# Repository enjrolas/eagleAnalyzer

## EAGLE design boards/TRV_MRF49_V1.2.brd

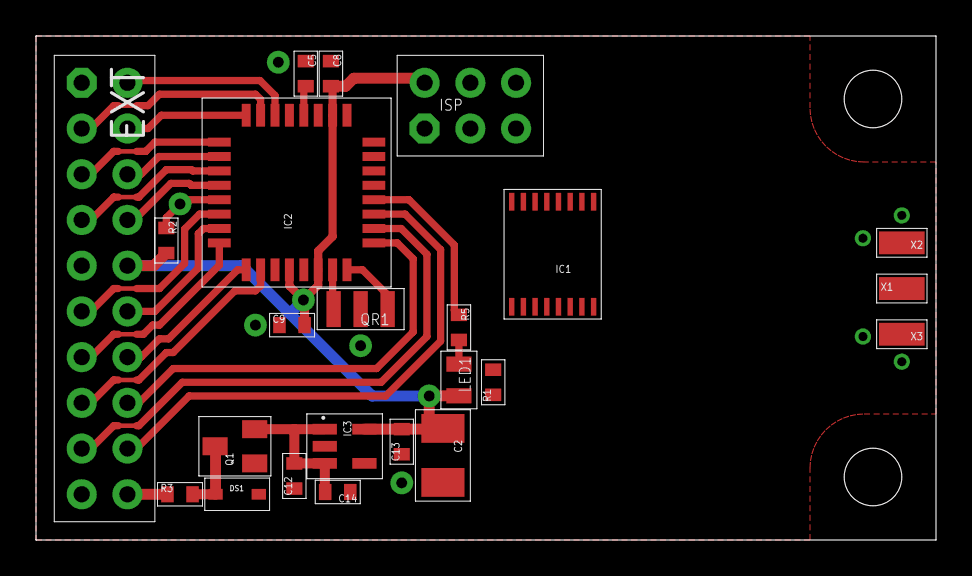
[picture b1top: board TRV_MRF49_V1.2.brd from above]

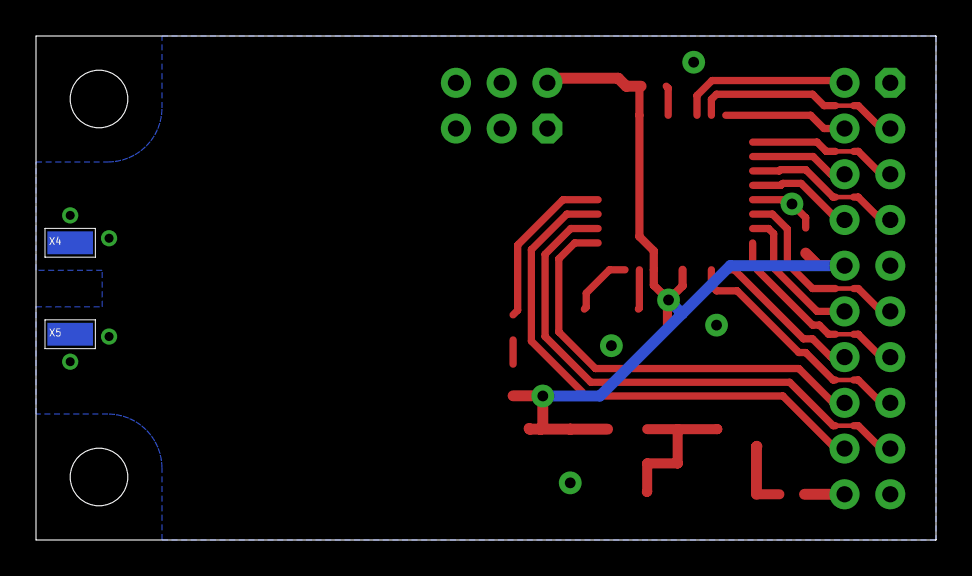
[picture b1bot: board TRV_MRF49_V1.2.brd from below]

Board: 2 copper layers, 50.0 x 28.0 mm, 25 parts (2 on the bottom side), 31 nets.

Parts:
C2: 10u; SMC_B
C5, C8, C9, C14: 100n; 0603
C12, C13: 1u; 0603
DS1: PESD12VL1BA; SOD323
EXT: EXT; ML20S
IC1: TSSOP16
IC2: MEGA328P-AU; TQFP32-08
IC3: LP2992-IM5-3.3; SOT23-5
ISP: ISP; ML6S
LED1: LEDR; 0805
Q1: IRLML9301; SOT23
QR1: 8M; CR
R1, R2: 10k; 0603
R3: 0R; 0603
R5: 330R; 0603
X1: ANT; S2.54/1.27
X2, X3, X4, X5: GND; S2.54/1.27

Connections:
+3V3: C2.+, C8.2, C9.2, C13.2, EXT.10, IC2.4, IC2.6, IC2.18, IC3.5, ISP.2, LED1.C, R1.1, R2.2
GND: C2.-, C5.1, C8.1, C9.1, C12.1, C13.1, C14.1, DS1.A, EXT.9, EXT.19, IC1.11, IC2.3, IC2.5, IC2.21, IC3.2, ISP.6, Q1.1, QR1.M, X2.1, X3.1, X4.1, X5.1
MISO: IC1.4, IC2.16, ISP.1
MOSI: IC1.1, IC2.15, ISP.4
unnamed: EXT.2, IC2.22
unnamed: DS1.C, Q1.3, R3.2
unnamed: C5.2, IC2.20
unnamed: IC2.8, QR1.1
unnamed: IC2.7, QR1.2
unnamed: EXT.20, R3.1
unnamed: IC2.12, R5.1
unnamed: C12.2, C14.2, IC3.1, IC3.3, Q1.2
unnamed: LED1.A, R5.2
PC0: EXT.3, IC2.23
PC1: EXT.4, IC2.24
PC2: EXT.5, IC2.25
PC3: EXT.6, IC2.26
PC4: EXT.7, IC2.27
PC5: EXT.8, IC2.28
PD2: EXT.13, IC2.32
PD3: EXT.14, IC2.1
PD4: EXT.15, IC2.2
PD5: EXT.16, IC2.9
PD6: EXT.17, IC2.10
PD7: EXT.18, IC2.11
RIRQ: IC1.5, IC2.13
RSEL: IC1.3, IC2.14, R1.2
RST: IC2.29, ISP.5, R2.1
RXD: EXT.11, IC2.30
SCK: IC1.2, IC2.17, ISP.3
TXD: EXT.12, IC2.31

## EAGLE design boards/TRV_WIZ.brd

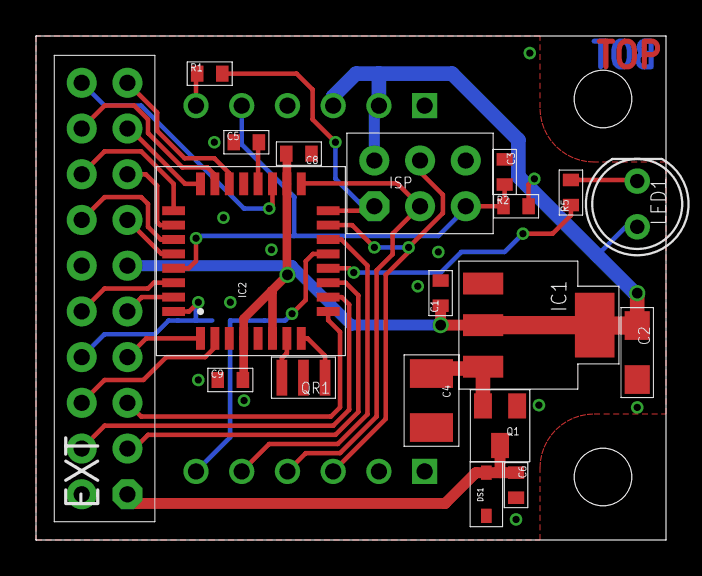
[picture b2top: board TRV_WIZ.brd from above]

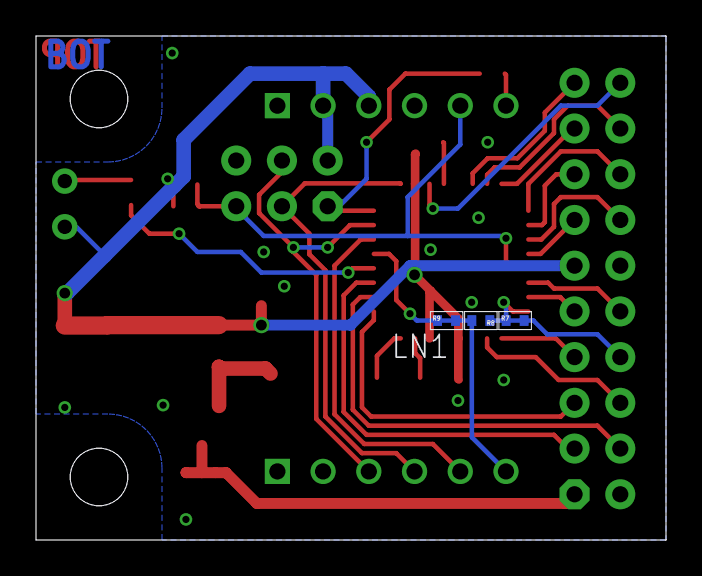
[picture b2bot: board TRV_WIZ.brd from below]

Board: 2 copper layers, 35.0 x 28.0 mm, 23 parts (4 on the bottom side), 32 nets.

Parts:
C1: 1u; 0603
C2: 10u 6V; SMC_A
C3, C5, C6, C8, C9: 100n; 0603
C4: 10u 20V; SMC_B
DS1: PESD12VL1BA; SOD323
EXT: EXT; ML20S
IC1: LD1117S33TR; SOT223
IC2: MEGA328P-AU; TQFP32-08
ISP: ISP; ML6S
LED1: LEDR; T1-3/4
LN1: WIZ820IO
Q1: IRLML9301TRPBF; SOT23
QR1: 8M; CSTCE
R1, R5: 330R; 0603
R2: 10k; 0603
R7, R8, R9: cfg; 0402

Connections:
+3V3: C1.1, C2.+, C8.2, C9.2, EXT.11, IC1.2, IC1.4, IC2.4, IC2.6, IC2.18, ISP.2, LED1.A, LN1.J2.2, LN1.J2.3, R2.2
GND: C1.2, C2.-, C3.1, C4.-, C5.1, C6.2, C8.1, C9.1, DS1.C, EXT.2, EXT.12, IC1.1, IC2.3, IC2.5, IC2.21, ISP.6, LN1.J1.1, LN1.J1.2, LN1.J2.1, Q1.1, QR1.G
MISO: IC2.16, ISP.1, R1.2
MOSI: IC2.15, ISP.4, LN1.J1.3
unnamed: LN1.J2.6, R1.1
unnamed: C6.1, DS1.A, EXT.1, Q1.3
unnamed: EXT.19, IC2.22
unnamed: C4.+, IC1.3, Q1.2
unnamed: C5.2, IC2.20
unnamed: IC2.8, QR1.A
unnamed: IC2.7, QR1.B
unnamed: IC2.12, R5.1
unnamed: EXT.8, IC2.32, R7.1, R7.2, R8.1
unnamed: EXT.20, IC2.19
unnamed: LED1.C, R5.2
PC0: EXT.18, IC2.23
PC1: EXT.17, IC2.24
PC2: EXT.16, IC2.25
PC3: EXT.15, IC2.26
PC4: EXT.14, IC2.27
PC5: EXT.13, IC2.28
PD3: EXT.7, IC2.1
PD4: EXT.6, IC2.2
PD5: EXT.5, IC2.9
PD6: EXT.4, IC2.10
PD7: EXT.3, IC2.11
RST: C3.2, IC2.29, ISP.5, LN1.J2.5, R2.1
RXD: EXT.10, IC2.30
SCK: IC2.17, ISP.3, LN1.J1.4
TXD: EXT.9, IC2.31
WIRQ: IC2.13, LN1.J1.6, R8.2, R9.1, R9.2
WSEL: IC2.14, LN1.J1.5

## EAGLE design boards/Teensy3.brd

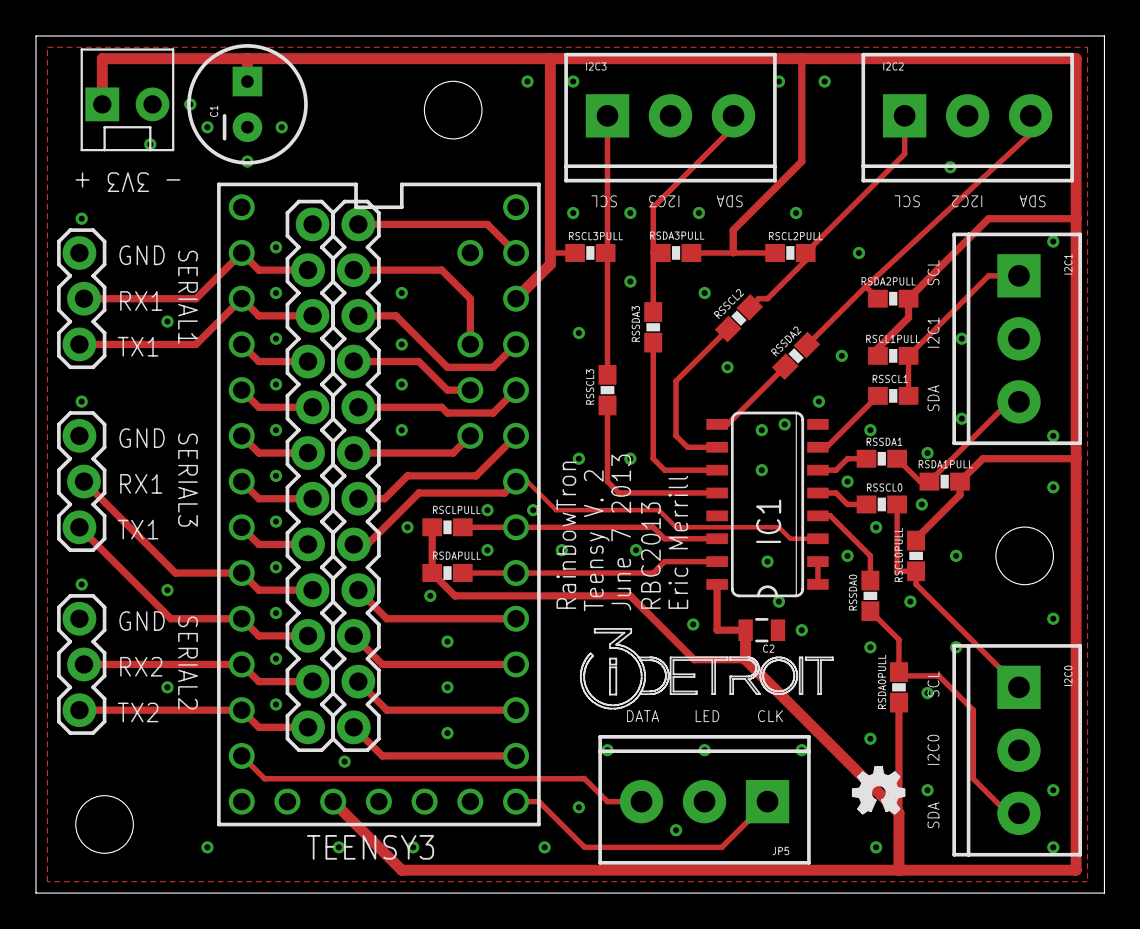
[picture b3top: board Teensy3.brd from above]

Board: 2 copper layers, 59.4 x 47.6 mm, 35 parts (0 on the bottom side), 45 nets.

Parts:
C1: CPOL-RADIAL-100UF-25V
C2: .1uF; 0805
I2C0, I2C1, I2C2, I2C3: SCREWTERMINAL-3.5MM-3
IC1: SO16
JP1, JP2: 1X12_LOCK
JP5: SCREWTERMINAL-3.5MM-3
PWR: MOLEX-1X2_LOCK
RSCL0PULL, RSCL1PULL, RSCL2PULL, RSCL3PULL: 3.3k; 0603-RES
RSCLPULL: 3.3k; 0603-RES
RSDA0PULL, RSDA1PULL, RSDA2PULL, RSDA3PULL: 3.3k; 0603-RES
RSDAPULL: 3.3k; 0603-RES
RSSCL0, RSSCL1, RSSCL2, RSSCL3: 200; 0603-RES
RSSDA0, RSSDA1, RSSDA2, RSSDA3: 200; 0603-RES
SERIAL1, SERIAL2, SERIAL3: 1X03_LOCK
TEENSY3: TEENSY_3.0+4
U$1: I3DETROITVEC14MM
U$2: OSHW_FILLX100_NOTEXT

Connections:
GND: C1.2, C2.1, I2C0.2, I2C1.2, I2C2.2, I2C3.2, IC1.1, IC1.2, IC1.8, IC1.13, JP1.12, JP5.2, PWR.2, SERIAL1.3, SERIAL2.3, SERIAL3.3, TEENSY3.GND, TEENSY3.GND1
unnamed: IC1.12, RSSCL3.1
unnamed: IC1.11, RSSDA3.1
unnamed: IC1.10, RSSCL2.1
unnamed: JP1.1, SERIAL2.1, TEENSY3.10
unnamed: IC1.9, RSSDA2.1
unnamed: IC1.7, RSSCL1.2
unnamed: IC1.6, RSSDA1.2
unnamed: IC1.5, RSSCL0.2
unnamed: IC1.4, RSSDA0.2
unnamed: JP1.2, SERIAL2.2, TEENSY3.9
unnamed: JP1.4, SERIAL3.2, TEENSY3.7
unnamed: JP1.3, SERIAL3.1, TEENSY3.8
unnamed: IC1.3, JP2.5, TEENSY3.20/A6
unnamed: JP5.3, TEENSY3.11
unnamed: JP1.5, TEENSY3.6
unnamed: JP1.6, TEENSY3.5
unnamed: JP1.7, TEENSY3.4
unnamed: JP1.8, TEENSY3.3
unnamed: JP1.9, TEENSY3.2
unnamed: JP2.1, TEENSY3.14/A0
unnamed: JP2.2, TEENSY3.15/A1
unnamed: JP5.1, TEENSY3.13
unnamed: JP2.3, TEENSY3.16/A2
unnamed: JP2.4, TEENSY3.17/A3
unnamed: JP2.6, TEENSY3.21/A7
unnamed: JP2.7, TEENSY3.A11
unnamed: JP2.8, TEENSY3.22/A8
unnamed: JP2.9, TEENSY3.A10
unnamed: JP2.10, TEENSY3.23/A9
unnamed: JP2.12, TEENSY3.AGND
unnamed: JP2.11, TEENSY3.AREF
RX1: JP1.11, SERIAL1.2, TEENSY3.0
SCL: IC1.14, RSCLPULL.2, TEENSY3.19/A5
SCL0: I2C0.1, RSCL0PULL.1, RSSCL0.1
SCL1: I2C1.1, RSCL1PULL.1, RSSCL1.1
SCL2: I2C2.1, RSCL2PULL.1, RSSCL2.2
SCL3: I2C3.1, RSCL3PULL.1, RSSCL3.2
SDA: IC1.15, RSDAPULL.2, TEENSY3.18/A4
SDA0: I2C0.3, RSDA0PULL.1, RSSDA0.1
SDA1: I2C1.3, RSDA1PULL.1, RSSDA1.1
SDA2: I2C2.3, RSDA2PULL.1, RSSDA2.2
SDA3: I2C3.3, RSDA3PULL.1, RSSDA3.2
TX1: JP1.10, SERIAL1.1, TEENSY3.1
VCC: C1.1, C2.2, IC1.16, PWR.1, RSCL0PULL.2, RSCL1PULL.2, RSCL2PULL.2, RSCL3PULL.2, RSCLPULL.1, RSDA0PULL.2, RSDA1PULL.2, RSDA2PULL.2, RSDA3PULL.2, RSDAPULL.1, TEENSY3.3.3V, TEENSY3.3.3V1

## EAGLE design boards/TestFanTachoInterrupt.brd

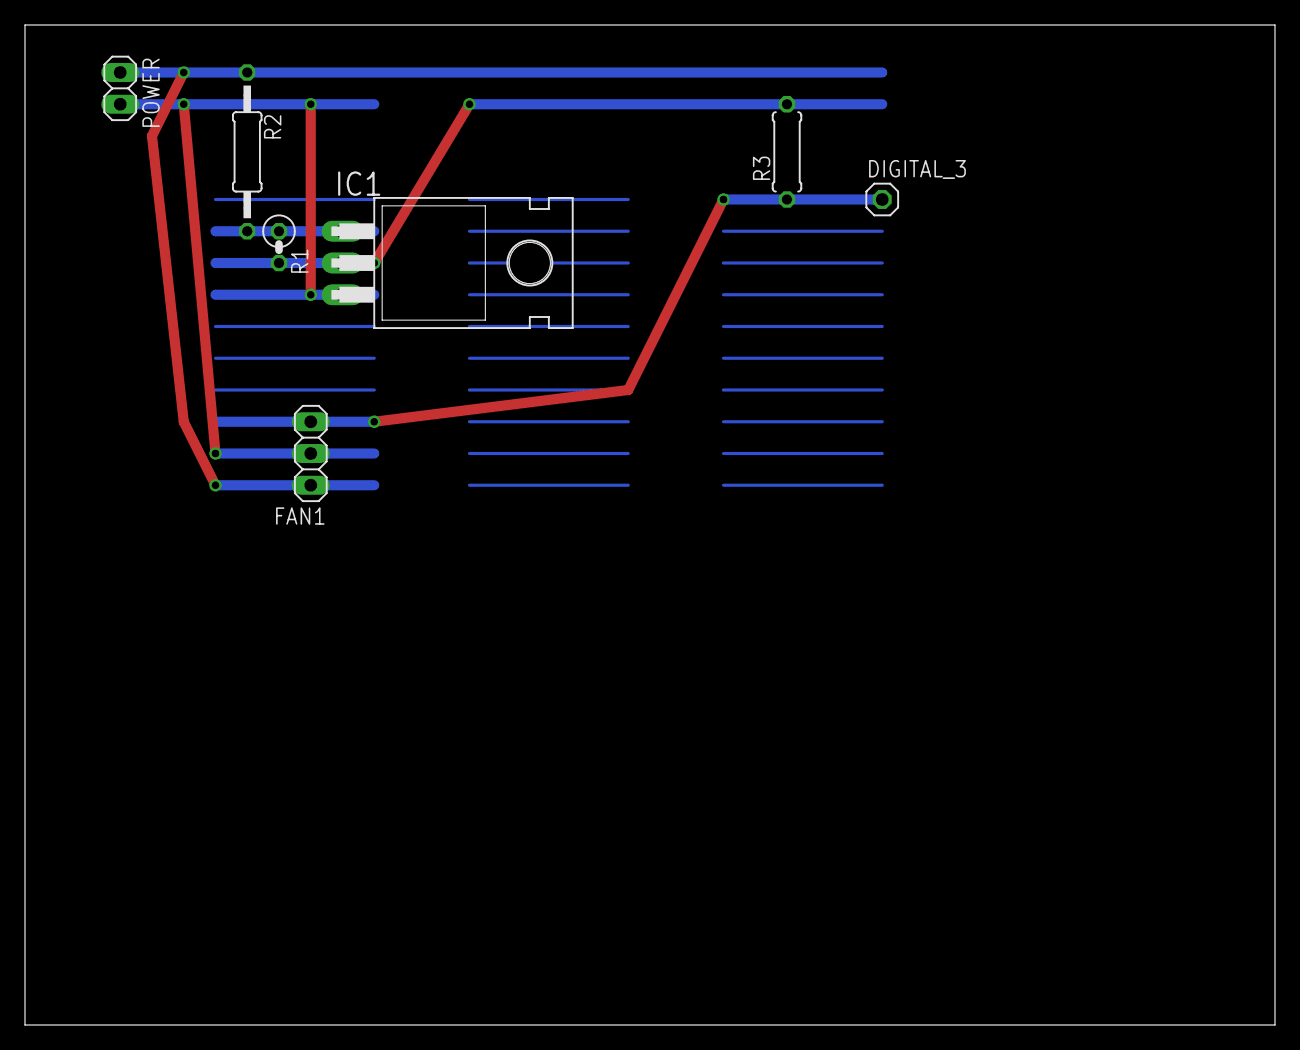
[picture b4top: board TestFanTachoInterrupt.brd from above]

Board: 2 copper layers, 100.0 x 80.0 mm, 7 parts (0 on the bottom side), 5 nets.

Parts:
DIGITAL_3: 1X01
FAN1: 1X03
IC1: 317T; TO220H
POWER: 1X02
R1: 330; 0207/2V
R2: 1k; 0207/12
R3: 10k; 0207/7

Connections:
+12V: FAN1.2, IC1.3, POWER.2
FAN1_TACHO: DIGITAL_3.1, FAN1.1, R3.1
GND: FAN1.3, POWER.1, R2.1
unnamed: IC1.1, R1.1, R2.2
VCC: IC1.2, R1.2, R3.2

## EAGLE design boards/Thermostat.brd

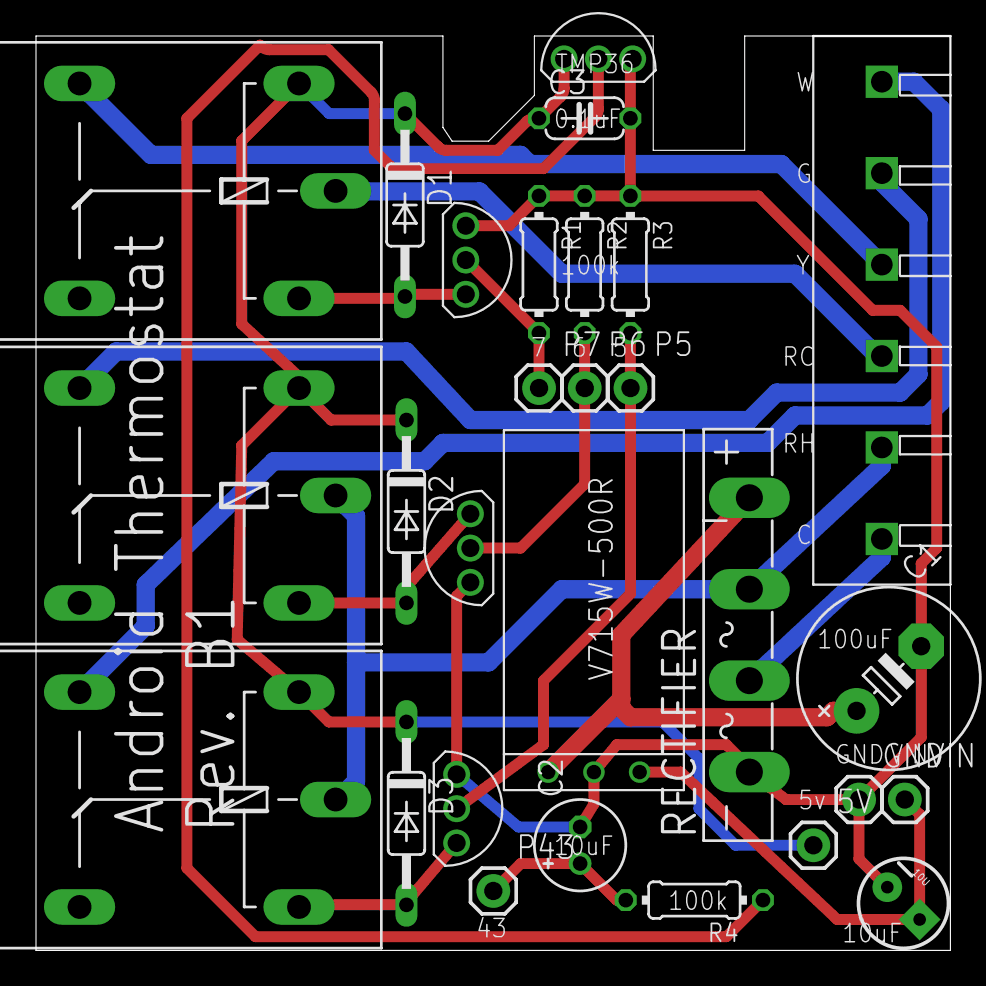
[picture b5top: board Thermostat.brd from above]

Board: 2 copper layers, 50.8 x 50.8 mm, 28 parts (0 on the bottom side), 18 nets.

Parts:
5V: 1X01
10U: CPOL-RADIAL-10UF-25V
C1: E5-10,5
C2: E2-5
C3: C050-024X044
D1, D2, D3: DO35-10
GND: 1X01
K1, K2, K3: G5LE
P5, P6, P7, P43: 1X01
R1, R2, R3, R4: 0204/7
RECTIFIER: GBU4S
U$1: TMP36
U$2: V715W-500R; SWITCHINGREGULATOR
U$3: PHOENIX-651-1935200; PHOENIX_E_5MM_6PIN
U$4, U$5, U$6: TRANSISTOR
VIN: 1X01

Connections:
+5V: 5V.1, C3.1, D1.C, D2.C, D3.C, K1.1, K2.1, K3.1, U$1.VC1
GND: 10U.2, C1.-, C2.-, C3.2, GND.1, R1.1, R2.1, R3.1, RECTIFIER.-, U$1.GND3, U$2.GND, U$4.S, U$5.S, U$6.S
unnamed: K1.P, U$3.P$3
unnamed: P6.1, R2.2, U$5.G
unnamed: D2.A, K2.2, U$5.D
unnamed: C2.+, P43.1, R4.2
unnamed: R4.1, U$1.OUT2
unnamed: P7.1, R1.2, U$6.G
unnamed: D1.A, K1.2, U$6.D
unnamed: K2.P, K3.P, RECTIFIER.AC1, U$3.P$2
unnamed: 10U.1, U$2.VO, VIN.1
unnamed: K3.S, U$3.P$6
unnamed: K1.S, U$3.P$4
unnamed: K2.S, U$3.P$5
unnamed: P5.1, R3.2, U$4.G
unnamed: D3.A, K3.2, U$4.D
unnamed: RECTIFIER.AC2, U$3.P$1
unnamed: C1.+, RECTIFIER.+, U$2.VI

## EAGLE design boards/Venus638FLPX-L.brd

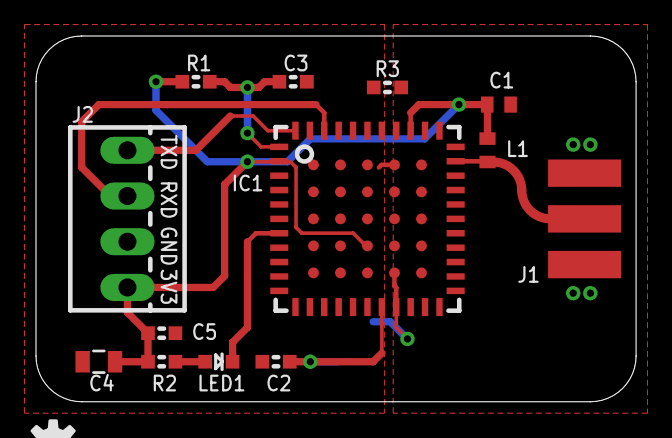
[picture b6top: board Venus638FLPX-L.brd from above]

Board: 2 copper layers, 33.3 x 20.3 mm, 15 parts (1 on the bottom side), 10 nets.

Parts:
B1: Keystone 3000; BATTCON_12MM
C1: 22pF; C0402
C2, C3, C5: 100nF; 0603
C4: 10µF; 0805
IC1: VENUS638FLPX-L; VENUS638FLPX
J1: Antenna; SMA-EDGE
J2: Interface; 22-23-2041
L1: 33nH; C0402
LED1: Status; LED-0603
R1: 33kΩ; 0603
R2: 470Ω; 0603
R3: 0Ω; 0603
SY: OSHW-LOGOS; OSHW-LOGO-S

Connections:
+3.3V: C1.2, C4.2, C5.2, IC1.2, IC1.36, IC1.58, J2.4, L1.1, R1.1, R2.1
ANT2: IC1.32, J1.SIG, L1.2
GND: B1.GND, C2.1, C3.1, C4.1, C5.1, IC1.8, IC1.9, IC1.10, IC1.11, IC1.15, IC1.19, IC1.49, IC1.60, IC1.64, J2.3, R3.1
unnamed: C3.2, IC1.1, R1.2
unnamed: B1.PWR@1, C2.2, IC1.18
unnamed: IC1.7, LED1.C
unnamed: LED1.A, R2.2
RFGND: C1.1, IC1.21, IC1.22, IC1.24, IC1.25, IC1.27, IC1.28, IC1.29, IC1.31, IC1.33, IC1.61, IC1.62, IC1.65, IC1.69, J1.GND@0, J1.GND@1, J1.GND@2, J1.GND@3, R3.2
RXD: IC1.42, J2.2
TXD: IC1.44, J2.1

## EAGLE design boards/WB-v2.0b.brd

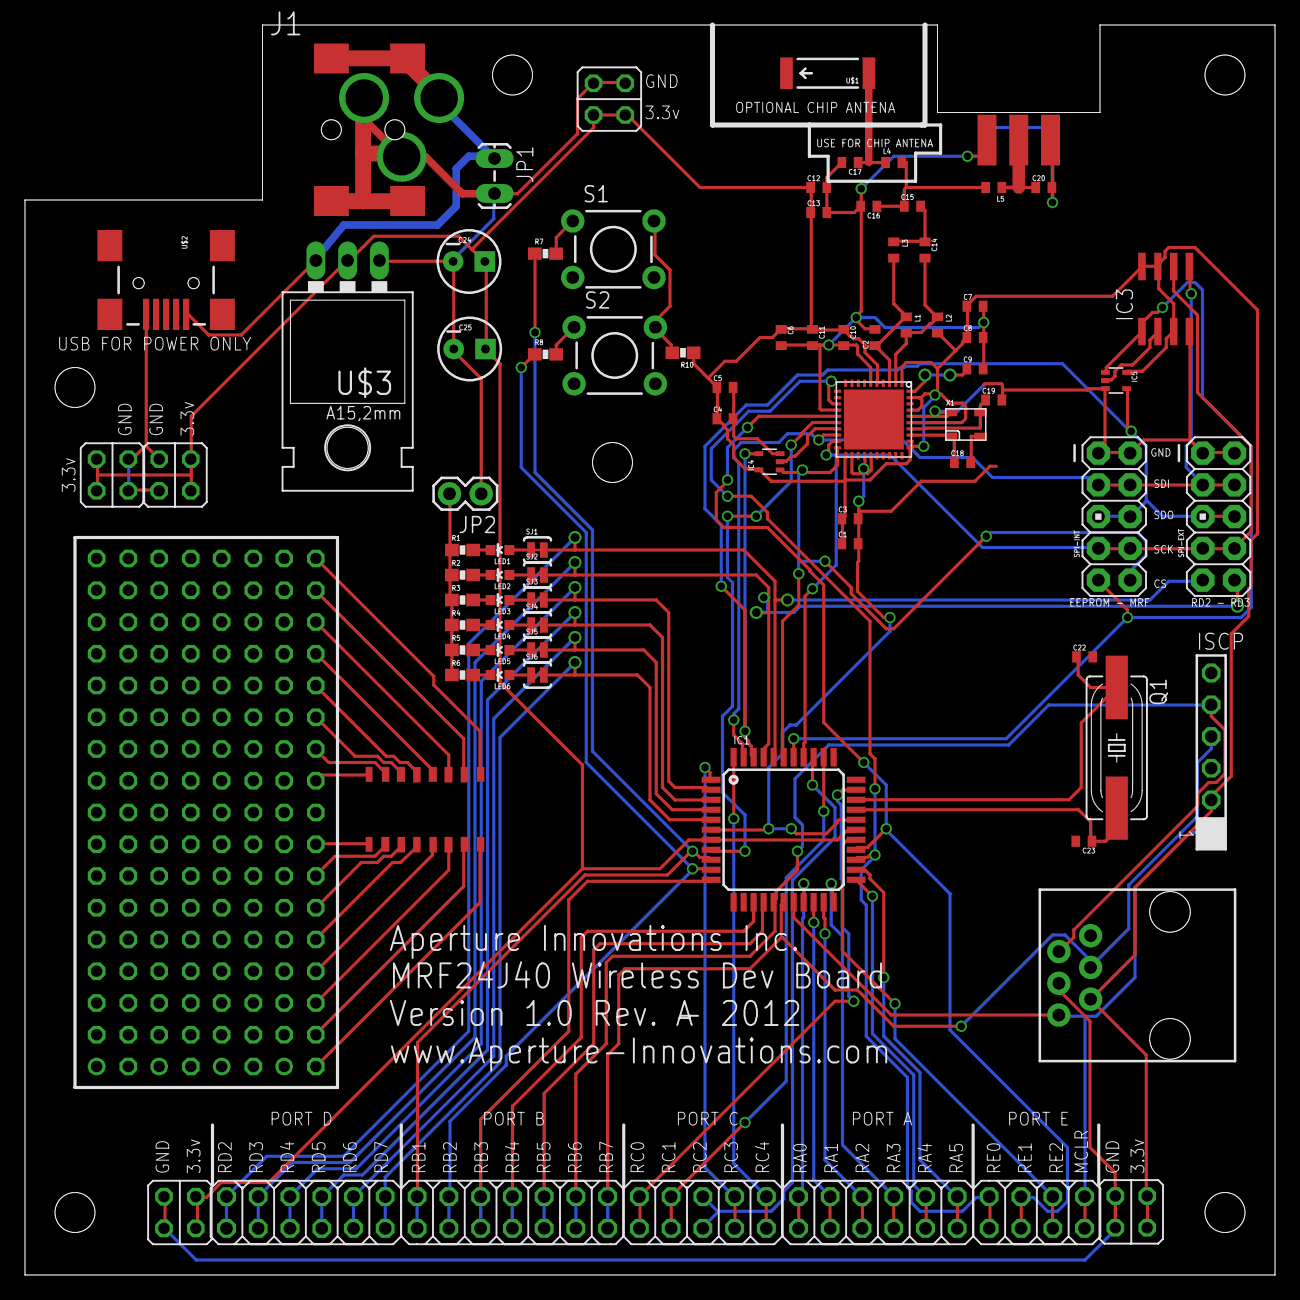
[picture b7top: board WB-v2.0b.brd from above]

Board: 2 copper layers, 100.0 x 100.0 mm, 84 parts (0 on the bottom side), 66 nets.

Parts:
C1, C3, C7: 0.01uF; C0402
C2, C14, C15, C16: 0.5pF; C0402
C4, C5, C6, C10: 47pF; C0402
C8: 1uF; C0402
C9: 100pF; C0402
C11: 0.1uF; C0402
C12: 0.01uf; C0402
C13: 47pf; C0402
C17, C20: 0.3pF; C0402
C18, C19, C22, C23: 18pF; C0402
C24: 47pf; CPOL-RADIAL-10UF-25V
C25: 0.01uf; CPOL-RADIAL-10UF-25V
IC1: PIC18F4455_TQFP; TQFP44
IC2: MRF24J40; QFN40
IC3: MCHP-25LC080; SO-08
IC4, IC5: 74AHCT1G125DCK; SC70-5
ICSP-RJ11: RJ11-6PTH; RJ11-6
ISCP: TSW-106-02-S-S
J1: POWER_JACKCOMBO; POWER_JACK_COMBO
J$1: SMA_EDGE; SMA-EDGE
JP1: 1X02_LOCK_LONGPADS
JP2: 1X02
JP3, JP4, JP5, JP6, JP7: JP2Q
L1, L2: 10nH; C0402
L3: 5.6nH; C0402
L4, L5: 4.7nH; C0402
LED1, LED2, LED3, LED4, LED5, LED6: LED-0603
PB1, PB2, PB3, PB4: FE17-2
PORT-A: MA06-2
PORT-B: MA07-2
PORT-C: MA05-2
PORT-D: MA06-2
PORT-E: MA04-2
Q1: SM49
R1, R2, R3, R4, R5, R6: 470; 0603-RES
R7, R8: 1k; 0603-RES
R10: 10k; 0603-RES
S1, S2: TACTILE-PTH
SJ1, SJ2, SJ3, SJ4, SJ5, SJ6: SJ_2S-TRACE
SPI-EXT: M05X2PTH; AVR_ICSP
SPI-INT: M05X2PTH; AVR_ICSP
U$1: ANTENNA2SMD5; ANTENNA-CHIP5
U$2: USB-MINIB-5PIN; USB-MINIB
U$3: 3.3V; 78XXL
X1: ABM8

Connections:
EEPROM-CS: IC1.38, IC3.1, IC5.1, SPI-INT.9
GND: C1.2, C2.2, C3.2, C4.2, C5.2, C6.2, C7.2, C8.2, C9.2, C10.2, C11.2, C12.2, C13.2, C16.2, C17.2, C18.2, C19.2, C20.2, C22.2, C23.2, C24.2, C25.2, IC1.6, IC1.29, IC2.6, IC2.14, IC2.22, IC2.24, IC2.25, IC2.36, IC3.4, IC4.3, IC5.3, ICSP-RJ11.3, ISCP.3, J1.GND, J1.GND@1, J$1.GND@0, J$1.GND@1, J$1.GND@2, J$1.GND@3, JP1.2, JP2.1, JP3.2, JP3.4, JP4.2, JP4.4, JP5.2, JP5.4, JP6.2, JP6.4, JP7.2, JP7.4, S1.3, S1.4, S2.3, S2.4, SPI-EXT.1, SPI-EXT.2, SPI-INT.1, SPI-INT.2, U$2.GND, U$3.IN, X1.P$2, X1.P$4
MCLR: IC1.18, ICSP-RJ11.1, ISCP.1, PORT-E.7, PORT-E.8
MRF-CS: IC1.39, IC2.20, IC4.1, SPI-INT.10
MRF-INT: IC1.8, IC2.16
unnamed: C14.1, C15.2, L3.1
unnamed: C2.1, IC2.3, L1.1, L3.2
unnamed: C14.2, IC2.2, L1.2, L2.1
unnamed: C15.1, C16.1, L4.2, L5.2
unnamed: C17.1, L4.1, U$1.FEED
unnamed: C9.1, IC2.40
unnamed: C18.1, IC2.33, X1.P$1
unnamed: C19.1, IC2.34, X1.P$3
unnamed: C20.1, J$1.SIG, L5.1
unnamed: IC2.17, IC4.2
unnamed: IC3.2, IC5.2
unnamed: C23.1, IC1.30, Q1.2
unnamed: C22.1, IC1.31, Q1.1
unnamed: LED1.C, R1.2
unnamed: LED2.C, R2.2
unnamed: LED3.C, R3.2
unnamed: LED4.C, R4.2
unnamed: LED5.C, R5.2
unnamed: LED6.C, R6.2
unnamed: R7.2, S1.1
unnamed: R10.2, S1.2, S2.2
unnamed: LED1.A, SJ1.1
unnamed: LED3.A, SJ3.1
unnamed: LED4.A, SJ4.1
unnamed: LED5.A, SJ5.1
unnamed: LED6.A, SJ6.1
unnamed: R8.2, S2.1
unnamed: LED2.A, SJ2.1
unnamed: JP2.2, R1.1, R2.1, R3.1, R4.1, R5.1, R6.1
RA0: IC1.19, PORT-A.1, PORT-A.2
RA1: IC1.20, PORT-A.3, PORT-A.4
RA2: IC1.21, PORT-A.5, PORT-A.6
RA3: IC1.22, PORT-A.7, PORT-A.8
RA4: IC1.23, PORT-A.9, PORT-A.10
RA5: IC1.24, PORT-A.11, PORT-A.12
RB1: IC1.9, PORT-B.1, PORT-B.2, R7.1
RB2: IC1.10, PORT-B.3, PORT-B.4, R8.1
RB3: IC1.11, PORT-B.5, PORT-B.6
RB4: IC1.14, PORT-B.7, PORT-B.8
RB5: IC1.15, PORT-B.9, PORT-B.10
RB6: IC1.16, ICSP-RJ11.5, ISCP.5, PORT-B.11, PORT-B.12
RB7: IC1.17, ICSP-RJ11.4, ISCP.4, PORT-B.13, PORT-B.14
RC0: IC1.32, PORT-C.1, PORT-C.2
RC1: IC1.35, PORT-C.3, PORT-C.4
RC2: IC1.36, PORT-C.5, PORT-C.6
RD2: IC1.40, PORT-D.1, PORT-D.2, SJ1.2, SPI-EXT.9
RD3: IC1.41, PORT-D.3, PORT-D.4, SJ2.2, SPI-EXT.10
RD4: IC1.2, PORT-D.5, PORT-D.6, SJ3.2
RD5: IC1.3, PORT-D.7, PORT-D.8, SJ4.2
RD6: IC1.4, PORT-D.9, PORT-D.10, SJ5.2
RD7: IC1.5, PORT-D.11, PORT-D.12, SJ6.2
RE0: IC1.25, IC2.13, PORT-E.1, PORT-E.2
RE1: IC1.26, IC2.15, PORT-E.3, PORT-E.4
RE2: IC1.27, PORT-E.5, PORT-E.6
RX: IC1.1, PORT-C.7, PORT-C.8
SCK: IC1.37, IC2.19, IC3.6, SPI-EXT.7, SPI-EXT.8, SPI-INT.7, SPI-INT.8
SDI: IC1.43, IC2.18, IC3.5, SPI-EXT.3, SPI-EXT.4, SPI-INT.3, SPI-INT.4
SDO: IC1.42, IC4.4, IC5.4, SPI-EXT.5, SPI-EXT.6, SPI-INT.5, SPI-INT.6
TX: IC1.44, PORT-C.9, PORT-C.10
VCC: C1.1, C3.1, C4.1, C5.1, C6.1, C7.1, C8.1, C10.1, C11.1, C12.1, C13.1, C24.1, C25.1, IC1.7, IC1.28, IC2.1, IC2.4, IC2.5, IC2.21, IC2.31, IC2.32, IC2.35, IC2.37, IC2.39, IC3.3, IC3.7, IC3.8, IC4.5, IC5.5, ICSP-RJ11.2, ISCP.2, JP3.1, JP3.3, JP4.1, JP4.3, JP5.1, JP5.3, JP6.1, JP6.3, JP7.1, JP7.3, L2.2, R10.1, U$3.GND
VIN: J1.POWER, JP1.1, U$2.VBUS, U$3.OUT

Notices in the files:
parts and their libraries:
SparkFun-Connectors: Licensing: CC v3.0 Share-Alike You are welcome to use this library for commercial purposes.
